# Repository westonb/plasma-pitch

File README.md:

# plasma-pitch

This project is a 6.78MHz (ISM band) plasma tweeter. It consists of a Class D audio modulator and a class E differential amplifier driving a resonator. 

# Hardware
Schematics/PCB files in kicad format are in the PCB folder. 

The PCB for the current hardware revision is on OSHPark: https://oshpark.com/shared_projects/XJNJnl8u

# Sofware
Compiled with and has a makefile for GCC

For the project to build you need to add the standard peripheral library and 
CMSIS library from ST to the lib folder.

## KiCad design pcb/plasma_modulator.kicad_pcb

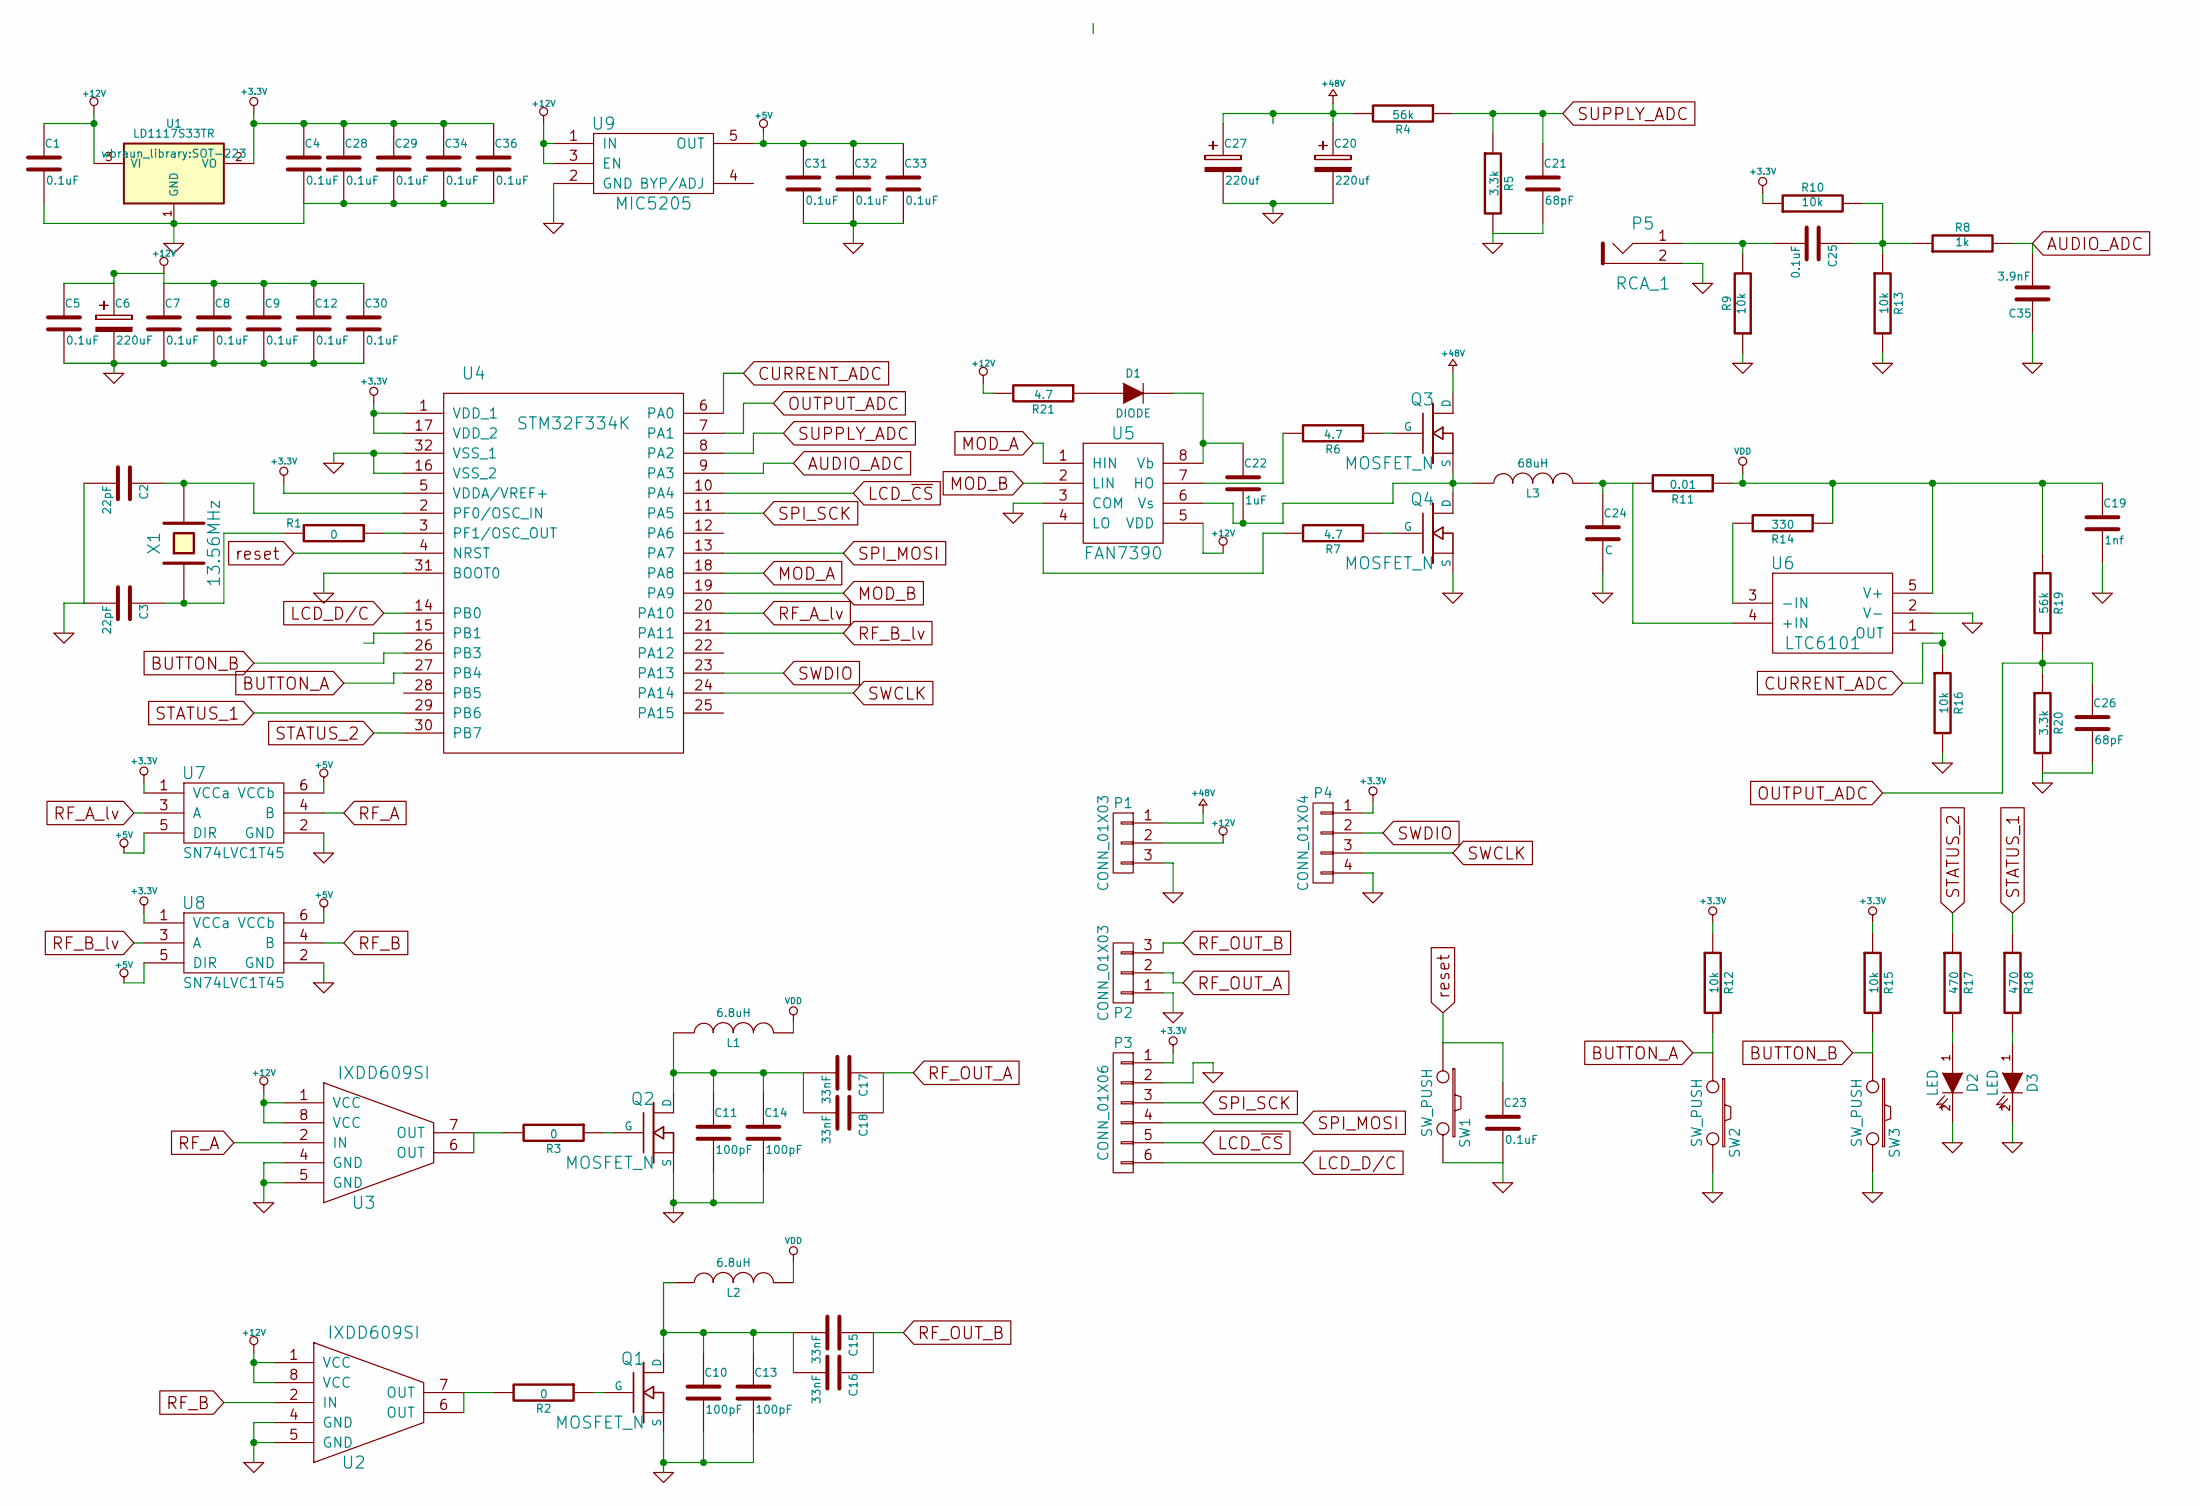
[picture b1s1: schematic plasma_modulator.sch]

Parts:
C1, C4, C5, C7, C8, C9, C12, C23, C25, C28, C29, C30, C31, C32, C33, C34, C36: 0.1uF; SMD-0805
C2, C3: 22pF; SMD-0805
C6: 220uF; Capacitor8x13RM3.8
C10, C11, C13, C14: 100pF; C_1206
C15, C16, C17, C18: 33nF; C_1206
C19: 1nf; C_1206
C20, C27: 220uf; Capacitor10x16RM5
C21, C26: 68pF; SMD-0805
C22: 1uF; SMD-0805
C24: C; Capacitor18x9x15mmRM15
C35: 3.9nF; SMD-0805
D1: DIODE; SOD-323
D2, D3: LED; LED-0805
L1, L2: 6.8uH; MSS1278
L3: 68uH; MSS1583
P1, P2: CONN_01X03; terminalBlock-5mm-3
P3: CONN_01X06; Pin_Header_Straight_1x06
P4: CONN_01X04; Pin_Header_Straight_1x04
P5: RCA_1; RCA
Q1, Q2, Q3, Q4: MOSFET_N; TO-220_FET-GDS_Vertical_LargePads
R1, R2, R3: 0; SMD-0805
R4, R19: 56k; SMD-0805
R5, R20: 3.3k; SMD-0805
R6, R7, R21: 4.7; SMD-0805
R8: 1k; SMD-0805
R9, R10, R12, R13, R15, R16: 10k; SMD-0805
R11: 0.01; R_1206
R14: 330; SMD-0805
R17, R18: 470; SMD-0805
SW1, SW2, SW3: SW_PUSH; button-5mm
U1: LD1117S33TR; SOT-223
U2, U3: IXDD609SI; SOIC-8_power
U4: STM32F334K; LQFP-32_7x7mm_Pitch0.8mm
U5: FAN7390; SOIC-8_3.9x4.9mm_Pitch1.27mm
U6: LTC6101; TSOT-23
U7, U8: SN74LVC1T45; SOT-23-6
U9: MIC5205; SOT-23-5
X1: 13.56MHz; 4-SMD

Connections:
+3.3V: C4.1, C28.1, C29.1, C34.1, C36.1, P3.1, P4.1, R10.1, R12.1, R15.1, U1.2 (VO), U4.1 (VDD_1), U4.5 (VDDA/VREF+), U4.17 (VDD_2), U7.1 (VCCa), U8.1 (VCCa)
+5V: C31.1, C32.1, C33.1, U7.5 (DIR), U7.6 (VCCb), U8.5 (DIR), U8.6 (VCCb), U9.5 (OUT)
+12V: C1.1, C5.1, C6.1, C7.1, C8.1, C9.1, C12.1, C30.1, P1.2, R21.2, U1.3 (VI), U2.1 (VCC), U2.8 (VCC), U3.1 (VCC), U3.8 (VCC), U5.5 (VDD), U9.1 (IN), U9.3 (EN)
+48V: C20.1, C27.1, P1.1, Q3.D, R4.2
AUDIO_ADC: C35.2, R8.2, U4.9 (PA3)
BUTTON_A: R12.2, SW2.1, U4.27 (PB4)
BUTTON_B: R15.2, SW3.1, U4.26 (PB3)
CURRENT_ADC: R16.1, U4.6 (PA0), U6.1 (OUT)
GND: C1.2, C2.2, C3.2, C4.2, C5.2, C6.2, C7.2, C8.2, C9.2, C10.2, C11.2, C12.2, C13.2, C14.2, C19.2, C20.2, C21.2, C23.2, C24.2, C26.2, C27.2, C28.2, C29.2, C30.2, C31.2, C32.2, C33.2, C34.2, C35.1, C36.2, D2.2 (K), D3.2 (K), P1.3, P2.1, P3.2, P4.4, P5.2, Q1.S, Q2.S, Q4.S, R5.2, R9.1, R13.2, R16.2, R20.2, SW1.2, SW2.2, SW3.2, U1.1 (GND), U2.4 (GND), U2.5 (GND), U2.9 (PAD), U3.4 (GND), U3.5 (GND), U3.9 (PAD), U4.16 (VSS_2), U4.31 (BOOT0), U4.32 (VSS_1), U5.3 (COM), U6.2 (V-), U7.2 (GND), U8.2 (GND), U9.2 (GND)
LCD_D/C: P3.6, U4.14 (PB0)
LCD_~CS~: P3.5, U4.10 (PA4)
MOD_A: U4.18 (PA8), U5.1 (HIN)
MOD_B: U4.19 (PA9), U5.2 (LIN)
unnamed: C2.1, U4.2 (PF0/OSC_IN), X1.2
unnamed: C3.1, R1.2, X1.1
unnamed: C10.1, C13.1, C15.2, C16.2, L2.1, Q1.D
unnamed: C11.1, C14.1, C17.2, C18.2, L1.1, Q2.D
unnamed: C22.1, D1.2 (K), U5.8 (Vb)
unnamed: C22.2, L3.1, Q3.S, Q4.D, U5.6 (Vs)
unnamed: C24.1, L3.2, R11.2, U6.4 (+IN)
unnamed: C25.1, R8.1, R10.2, R13.1
unnamed: C25.2, P5.1, R9.2
unnamed: D1.1 (A), R21.1
unnamed: D2.1 (A), R17.2
unnamed: D3.1 (A), R18.2
unnamed: Q1.G, R2.1
unnamed: Q2.G, R3.1
unnamed: Q3.G, R6.1
unnamed: Q4.G, R7.1
unnamed: R1.1, U4.3 (PF1/OSC_OUT)
unnamed: R2.2, U2.6 (OUT), U2.7 (OUT)
unnamed: R3.2, U3.6 (OUT), U3.7 (OUT)
unnamed: R6.2, U5.7 (HO)
unnamed: R7.2, U5.4 (LO)
unnamed: R14.2, U6.3 (-IN)
OUTPUT_ADC: C26.1, R19.2, R20.1, U4.7 (PA1)
RF_A: U3.2 (IN), U7.4 (B)
RF_A_lv: U4.20 (PA10), U7.3 (A)
RF_B: U2.2 (IN), U8.4 (B)
RF_B_lv: U4.21 (PA11), U8.3 (A)
RF_OUT_A: C17.1, C18.1, P2.2
RF_OUT_B: C15.1, C16.1, P2.3
SPI_MOSI: P3.4, U4.13 (PA7)
SPI_SCK: P3.3, U4.11 (PA5)
STATUS_1: R18.1, U4.29 (PB6)
STATUS_2: R17.1, U4.30 (PB7)
SUPPLY_ADC: C21.1, R4.1, R5.1, U4.8 (PA2)
SWCLK: P4.3, U4.24 (PA14)
SWDIO: P4.2, U4.23 (PA13)
VDD: C19.1, L1.2, L2.2, R11.1, R14.1, R19.1, U6.5 (V+)
reset: C23.1, SW1.1, U4.4 (NRST)

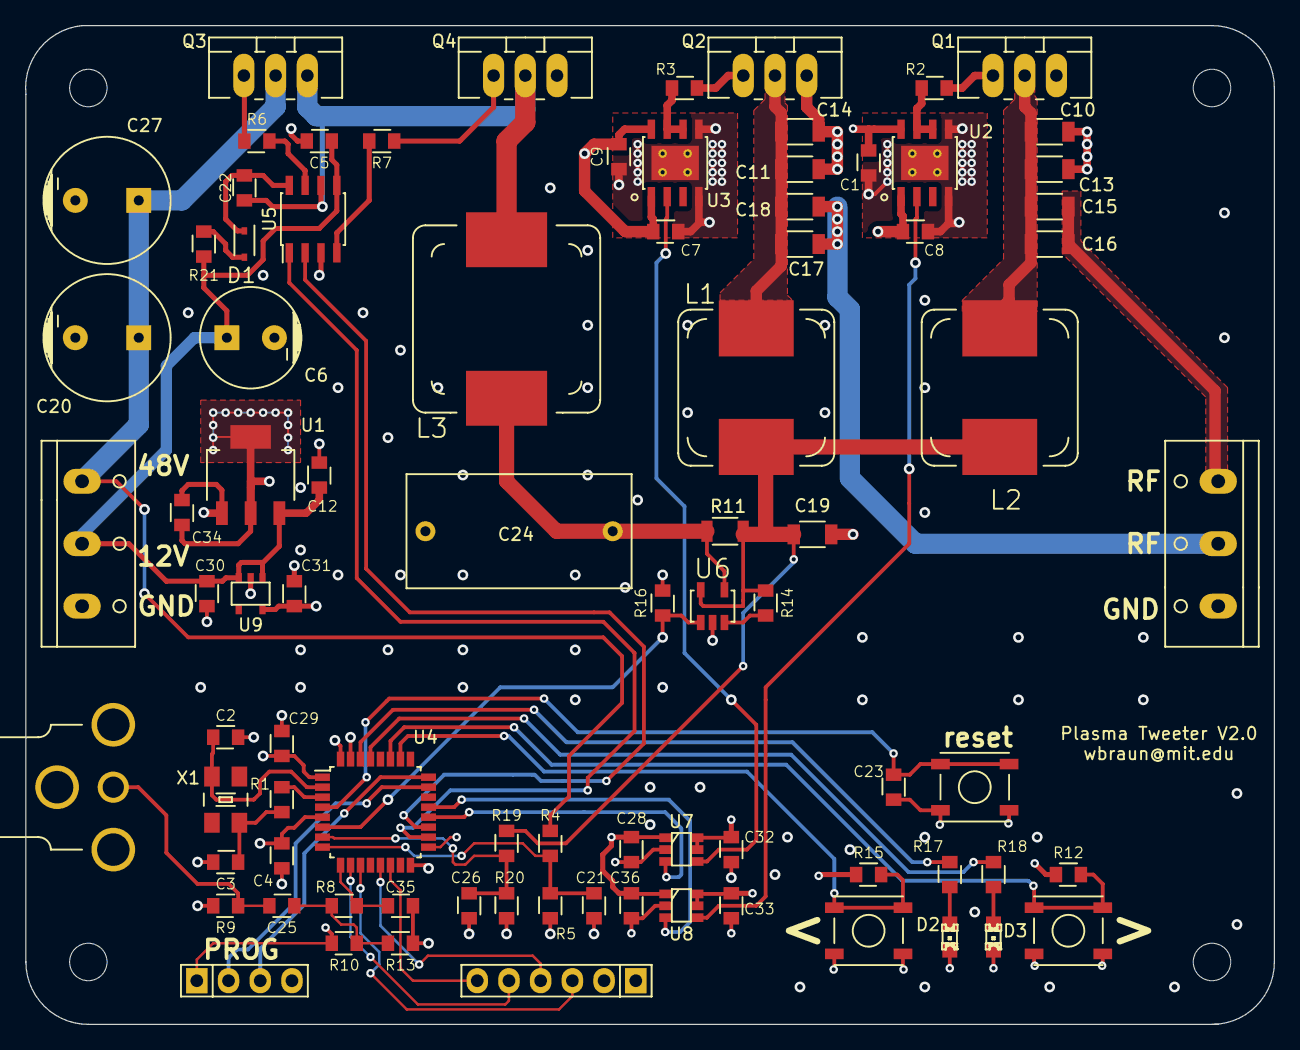
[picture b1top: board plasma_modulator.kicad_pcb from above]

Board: 4 copper layers, 100.0 x 80.0 mm, 89 parts (0 on the bottom side), 51 nets.

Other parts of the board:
MountingHole_3mm, MountingHole_3mm#2, MountingHole_3mm#3, MountingHole_3mm#4: VAL**; MountingHole_3mm

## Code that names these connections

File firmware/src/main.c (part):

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APB1 = 33.9MHz

Pins:
LCD_D/C: PB0
Button_B: PB3
Button_A: PB4
LED_1: PB6
LED_2: PB7

CURRENT_ADC: PA0 ADC1_IN1
OUTPUT_ADC: PA1 ADC1_IN2
SUPPLY_ADC: PA2 ADC1_IN3
AUDIO_ADC: PA3 ADC1_IN4

LCD_CS!: PA4
SPI_SCK: PA5
SPI_MOSI: PA7
MOD_A: PA8  HRTIM1_CHA1
MOD_B: PA9  HRTIM1_CHA2
RF_A: PA10  HRTIM1_CHB1
RF_B: PA11  HRTIM1_CHB2
*/


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}


//CURRENT_ADC: PA0 ADC1_IN1
//OUTPUT_ADC: PA1 ADC1_IN2
//SUPPLY_ADC: PA2 ADC1_IN3
//AUDIO_ADC: PA3 ADC1_IN4
void ADC_config(){

	ADC_InitTypeDef       ADC_InitStructure;
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	//HRTIM_ADCTRG2 event
	ADC_InjectedInitStruct.ADC_ExternalTrigInjecConvEvent = ADC_ExternalTrigInjecConvEvent_9;
  	ADC_InjectedInitStruct.ADC_ExternalTrigInjecEventEdge = ADC_ExternalTrigInjecEventEdge_RisingEdge;
  	ADC_InjectedInitStruct.ADC_InjecSequence1 = ADC_InjectedChannel_1; /* corresponds to PA0 (CURRENT_ADC) */
  	ADC_InjectedInitStruct.ADC_InjecSequence2 = ADC_InjectedChannel_2; /* corresponds to PA1 (OUTPUT_ADC) */
	ADC_InjectedInitStruct.ADC_InjecSequence3 = ADC_InjectedChannel_3; /* corresponds to PA2 (SUPPLY_ADC) */
  	ADC_InjectedInitStruct.ADC_InjecSequence4 = ADC_InjectedChannel_4; /* corresponds to PA3 (AUDIO_ADC) */
  	ADC_InjectedInitStruct.ADC_NbrOfInjecChannel = 4;
  	ADC_InjectedInit(ADC1, &ADC_InjectedInitStruct);
	
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}


//MOD_A: PA8  HRTIM1_CHA1
//MOD_B: PA9  HRTIM1_CHA2
void SMPS_config(){

	HRTIM_OutputCfgTypeDef HRTIM_TIM_OutputStructure;
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	//init GPIO pin 
	GPIO_InitTypeDef GPIO_InitStruct;

	//LED_1: PB6
	GPIO_ResetBits(GPIOB,GPIO_Pin_6);
	GPIO_InitStruct.GPIO_Pin = GPIO_Pin_6;
	GPIO_InitStruct.GPIO_Mode = GPIO_Mode_OUT;
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	GPIO_InitStruct.GPIO_PuPd = GPIO_PuPd_NOPULL;
	GPIO_Init(GPIOB,&GPIO_InitStruct);

	//LED_2: PB7
	GPIO_ResetBits(GPIOB,GPIO_Pin_7);
	GPIO_InitStruct.GPIO_Pin = GPIO_Pin_7;
	GPIO_InitStruct.GPIO_Mode = GPIO_Mode_OUT;
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	GPIO_InitStruct.GPIO_PuPd = GPIO_PuPd_NOPULL;
	GPIO_Init(GPIOB,&GPIO_InitStruct);
	
	//MOD_A: PA8, uses HRTIMER
	GPIO_ResetBits(GPIOA,GPIO_Pin_8);
	GPIO_InitStruct.GPIO_Pin = GPIO_Pin_8;
	GPIO_InitStruct.GPIO_Mode = GPIO_Mode_AF;
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	// HRTIMER is on AF_13
	GPIO_PinAFConfig(GPIOA, GPIO_PinSource8, GPIO_AF_13);

	//MOD_B: PA9, uses HRTIMER
	GPIO_ResetBits(GPIOA,GPIO_Pin_9);
	GPIO_InitStruct.GPIO_Pin = GPIO_Pin_9;
	GPIO_InitStruct.GPIO_Mode = GPIO_Mode_AF;
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	// HRTIMER is on AF_13
	GPIO_PinAFConfig(GPIOA, GPIO_PinSource9, GPIO_AF_13);
	
	//RF_A: PA10, uses HRTIMER
	GPIO_ResetBits(GPIOA,GPIO_Pin_10);
	GPIO_InitStruct.GPIO_Pin = GPIO_Pin_10;
	GPIO_InitStruct.GPIO_Mode = GPIO_Mode_AF;
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	// HRTIMER is on AF_13
	GPIO_PinAFConfig(GPIOA, GPIO_PinSource10, GPIO_AF_13);

	//RF_B: PA11, uses HRTIMER
	GPIO_ResetBits(GPIOA,GPIO_Pin_11);
	GPIO_InitStruct.GPIO_Pin = GPIO_Pin_11;
	GPIO_InitStruct.GPIO_Mode = GPIO_Mode_AF;
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
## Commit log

2015-03-09 first commit. Added PCB files from previous project
2015-03-09 fixed ISR table
2015-03-10 ADC and system timer work
2015-03-12 Audio modulation working w/o feedback
2015-04-15 Added matlab model, closed loop control
2015-05-05 calculated correct control loop constants, modulator is now stable
2015-05-15 optimized modulator ISR
2016-10-28 makefile change
2016-10-28 plotted schematic and PCB layouts
2016-11-27 added schematic
